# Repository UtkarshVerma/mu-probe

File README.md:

# μProbe

This probe is my personal take on the [Black Magic Debug][bmp] project's [Black Magic Probe v2.1][bmp-2.1]. I was disappointed to find out that I could not use my STLink v3 on non-ST targets[^1], even when they used the same protocol. One thing led to another and I stumbled upon the Black Magic Probe. The idea of having a configurable debugger appealed to me. This combined with an itch to work on a hardware project is what brought μProbe into existence.

> [!note]
> Please buy the official Black Magic Probe if you can! It is necessary to support the awesome work that the folks at the Black Magic project do.

## Possible future improvements

- Improve nASSERT_TVREF circuitry.
- Switch to a more powerful MCU.
- Add USB-C power negotiation.
- Add AUX connector from BMP v2.3.

## Credits

This project would not have been possible without the following resources:

- [Black Magic Debug v2.1e schematic][bmp]
- 3D models:
  - [4-pin SMT crystal osciallator by Steven Minichiello][xtal]

Lastly, I would also like to thank the warm community at 1BitSquared's Discord server for their insights and help.

[bmp]: https://black-magic.org/
[bmp-2.1]: https://black-magic.org/hardware.html#black-magic-probe-mini-v2-1-bmp21
[xtal]: https://grabcad.com/library/sitime-2016-4-pin-smt-mems-crystal-oscillator-to-20-ppm-1

[^1]: https://sourceforge.net/p/openocd/tickets/275/

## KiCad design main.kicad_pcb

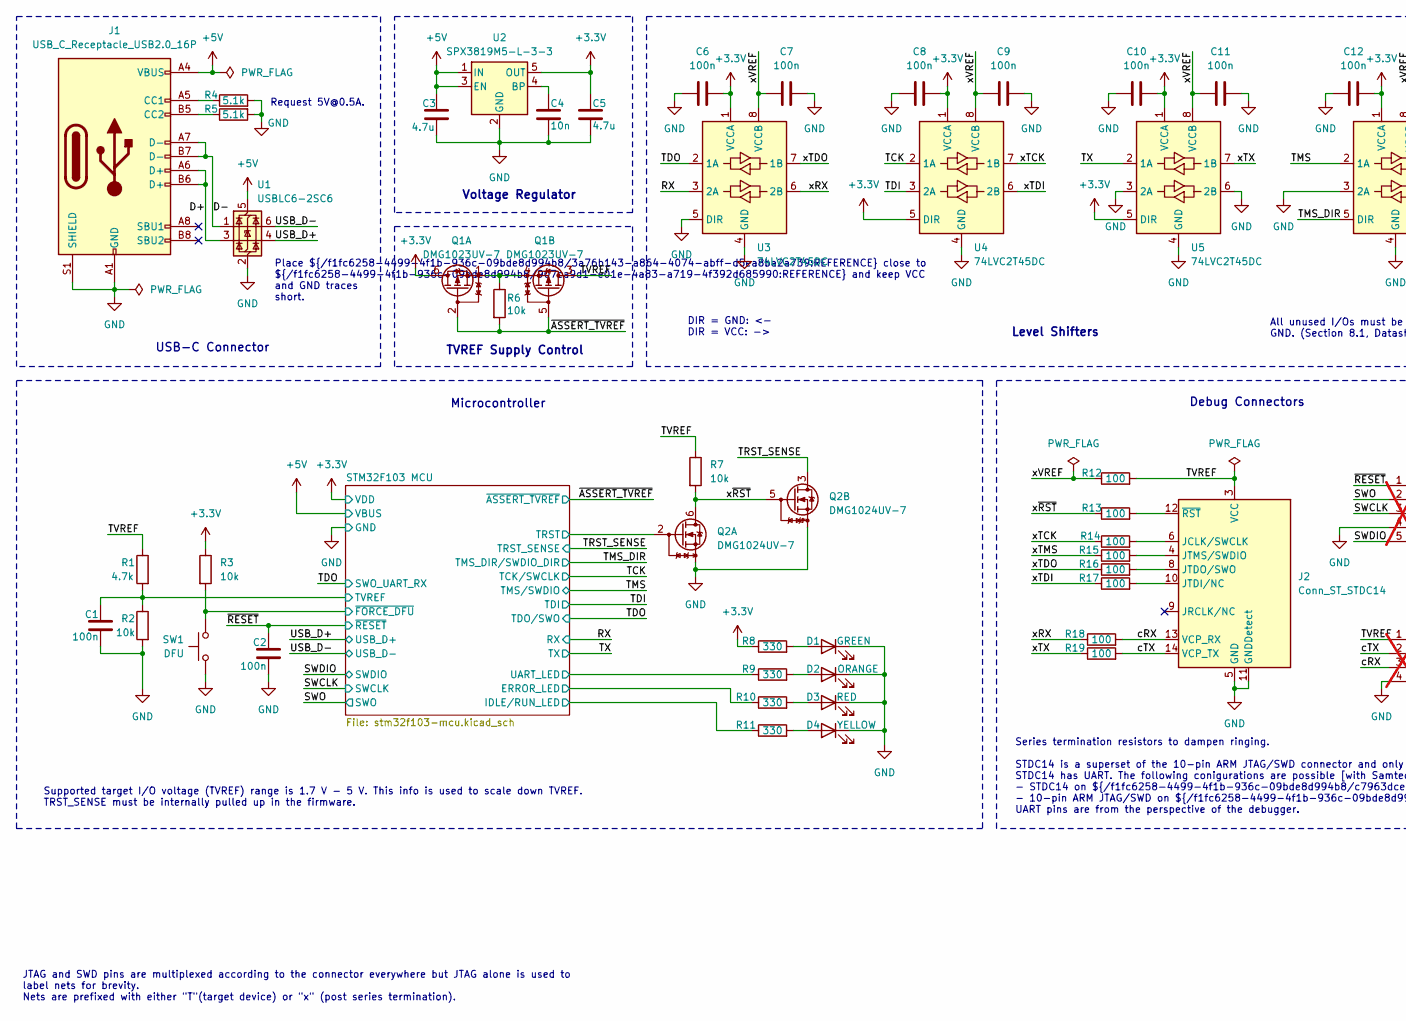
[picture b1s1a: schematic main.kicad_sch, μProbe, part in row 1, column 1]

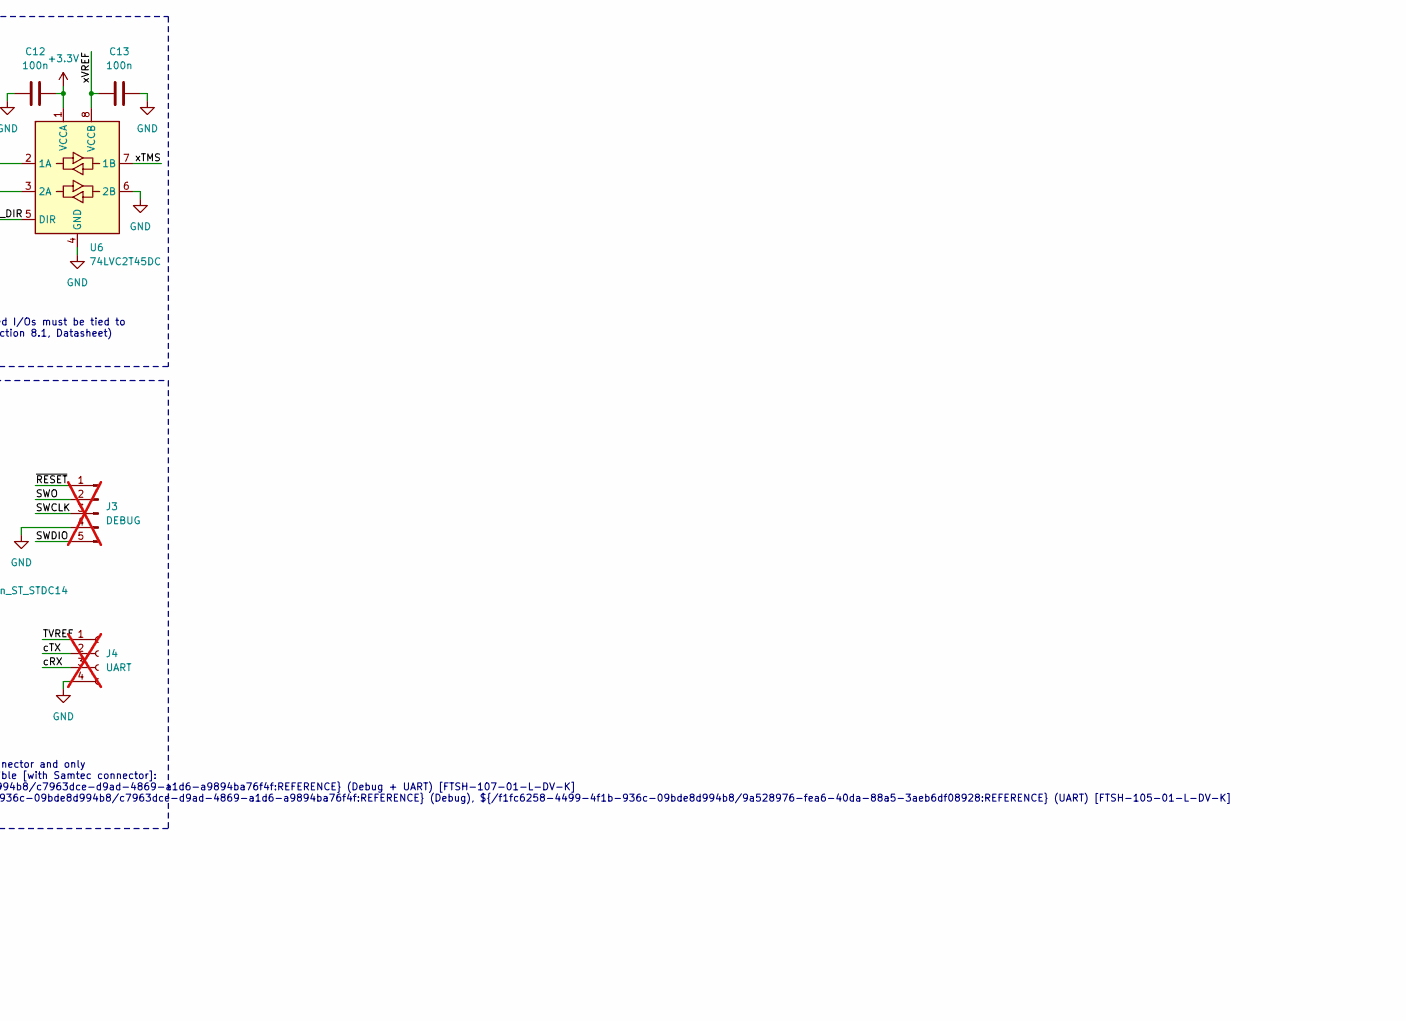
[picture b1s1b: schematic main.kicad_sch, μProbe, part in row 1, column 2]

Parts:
C1, C2, C6, C7, C8, C9, C10, C11, C12, C13: 100n; C_0402_1005Metric; LCSC Part C60474
C3, C5: 4.7u; C_0402_1005Metric; LCSC Part C23733
C4: 10n; C_0402_1005Metric; LCSC Part C15195
D1: GREEN; LED_0402_1005Metric; LCSC Part C2980183
D2: ORANGE; LED_0402_1005Metric; LCSC Part C779448
D3: RED; LED_0402_1005Metric; LCSC Part C136765
D4: YELLOW; LED_0402_1005Metric; LCSC Part C20608782
J1: USB_C_Receptacle_USB2.0_16P; USB_C_Receptacle_GCT_USB4105-xx-A_16P_TopMnt_Horizontal; LCSC Part C2988369
J2: Conn_ST_STDC14; SAMTEC_FTSH-107-01-L-DV-K; LCSC Part C46971079
J3: DEBUG; PinHeader_1x05_P1.27mm_Vertical; not fitted
J4: UART; PinHeader_1x04_P1.27mm_Vertical; not fitted
Q1: DMG1023UV-7; SOTFL50P162X60-6N; LCSC Part C212298
Q2: DMG1024UV-7; SOTFL50P162X60-6N; LCSC Part C2759893
R1: 4.7k; R_0402_1005Metric; LCSC Part C105871
R2, R3, R6, R7: 10k; R_0402_1005Metric; LCSC Part C60490
R4, R5: 5.1k; R_0402_1005Metric; LCSC Part C25905
R8, R9, R10, R11: 330; R_0402_1005Metric; LCSC Part C105875
R12, R13, R14, R15, R16, R17, R18, R19: 100; R_0402_1005Metric; LCSC Part C106232
SW1: DFU; SW_Push_SPST_NO_Alps_SKRK; LCSC Part C720477
U1: USBLC6-2SC6; SOT-23-6; LCSC Part C7519
U2: SPX3819M5-L-3-3; SOT-23-5; LCSC Part C9055
U3, U4, U5, U6: 74LVC2T45DC; VSSOP-8_2.3x2mm_P0.5mm; LCSC Part C15741

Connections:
+3.3V: C5.1, C6.1, C8.1, C10.1, C12.1, Q1.6 (D), R3.1, R8.1, U2.5 (OUT), U3.1 (VCCA), U4.1 (VCCA), U4.5 (DIR), U5.1 (VCCA), U5.5 (DIR), U6.1 (VCCA); also elsewhere on the board
+5V: C3.1, J1.A4 (VBUS), J1.A9 (VBUS), J1.B4 (VBUS), J1.B9 (VBUS), U1.5 (VBUS), U2.1 (IN), U2.3 (EN); also elsewhere on the board
/D+: J1.A6 (D+), J1.B6 (D+), U1.3 (I/O2)
/D-: J1.A7 (D-), J1.B7 (D-), U1.1 (I/O1)
/RX: U3.3 (2A); also elsewhere on the board
/STM32F103 MCU/ERROR_LED: R10.1; also elsewhere on the board
/STM32F103 MCU/IDLE/RUN_LED: R11.1; also elsewhere on the board
/STM32F103 MCU/TRST: Q2.2 (G); also elsewhere on the board
/STM32F103 MCU/TVREF: C1.1, R1.2, R2.1; also elsewhere on the board
/STM32F103 MCU/UART_LED: R9.1; also elsewhere on the board
/STM32F103 MCU/~FORCE_DFU: R3.2, SW1.2; also elsewhere on the board
/SWCLK: J3.3; also elsewhere on the board
/SWDIO: J3.5; also elsewhere on the board
/SWO: J3.2; also elsewhere on the board
/TCK: U4.2 (1A); also elsewhere on the board
/TDI: U4.3 (2A); also elsewhere on the board
/TDO: U3.2 (1A); also elsewhere on the board
/TMS: U6.2 (1A); also elsewhere on the board
/TMS_DIR: U6.5 (DIR); also elsewhere on the board
/TRST_SENSE: Q2.3 (D); also elsewhere on the board
/TVREF: J2.3 (VCC), J4.1, Q1.3 (D), R1.1, R7.1, R12.2
/TX: U5.2 (1A); also elsewhere on the board
/USB_D+: U1.4 (I/O2); also elsewhere on the board
/USB_D-: U1.6 (I/O1); also elsewhere on the board
/cRX: J2.13 (VCP_RX), J4.3, R18.2
/cTX: J2.14 (VCP_TX), J4.2, R19.2
/xRX: R18.1, U3.6 (2B)
/xTCK: R14.1, U4.7 (1B)
/xTDI: R17.1, U4.6 (2B)
/xTDO: R16.1, U3.7 (1B)
/xTMS: R15.1, U6.7 (1B)
/xTX: R19.1, U5.7 (1B)
/xVREF: C7.2, C9.2, C11.2, C13.2, R12.1, U3.8 (VCCB), U4.8 (VCCB), U5.8 (VCCB), U6.8 (VCCB)
/x~RST: Q2.5 (G), Q2.6 (D), R7.2, R13.1
/~ASSERT_TVREF: Q1.2 (G), Q1.5 (G), R6.2; also elsewhere on the board
/~RESET: C2.2, J3.1; also elsewhere on the board
GND: C1.2, C2.1, C3.2, C4.2, C5.2, C6.2, C7.1, C8.2, C9.1, C10.2, C11.1, C12.2, C13.1, D1.1 (K), D2.1 (K), D3.1 (K), D4.1 (K), J1.A1 (GND), J1.A12 (GND), J1.B1 (GND), J1.B12 (GND), J1.S1 (SHIELD), J2.5 (GND), J2.7 (GND), J2.11 (GNDDetect), J3.4, J4.4, Q2.1 (S), Q2.4 (S), R2.2, R4.2, R5.2, SW1.1, U1.2 (GND), U2.2 (GND), U3.4 (GND), U3.5 (DIR), U4.4 (GND), U5.3 (2A), U5.4 (GND), U5.6 (2B), U6.3 (2A), U6.4 (GND), U6.6 (2B); also elsewhere on the board
unnamed: D1.2 (A), R8.2
unnamed: D2.2 (A), R9.2
unnamed: D3.2 (A), R10.2
unnamed: D4.2 (A), R11.2
unnamed: J1.A5 (CC1), R4.1
unnamed: J1.B5 (CC2), R5.1
unnamed: J2.6 (JCLK/SWCLK), R14.2
unnamed: J2.10 (JTDI/NC), R17.2
unnamed: J2.8 (JTDO/SWO), R16.2
unnamed: J2.4 (JTMS/SWDIO), R15.2
unnamed: J2.12 (~RST), R13.2
unnamed: Q1.1 (S), Q1.4 (S), R6.1
unnamed: C4.1, U2.4 (BP)

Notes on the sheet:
Debug Connectors
TVREF Supply Control
Request 5V@0.5A.
Series termination resistors to dampen ringing. STDC14 is a superset of the 10-pin ARM JTAG/SWD connector and only STDC14 has UART. The following conigurations are possible [with Samtec connector]: - STDC14 on ${/f1fc6258-4499-4f1b-936c-09bde8d994b8/c7963dce-d9ad-4869-a1d6-a9894ba76f4f:REFERENCE} (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
Level Shifters
All unused I/Os must be tied to GND. (Section 8.1, Datasheet)
JTAG and SWD pins are multiplexed according to the connector everywhere but JTAG alone is used to label nets for brevity. Nets are prefixed with either "T"(target device) or "x" (post series termination).
USB-C Connector
Supported target I/O voltage (TVREF) range is 1.7 V - 5 V. This info is used to scale down TVREF. TRST_SENSE must be internally pulled up in the firmware.
Place ${/f1fc6258-4499-4f1b-936c-09bde8d994b8/3a76b143-a864-4074-abff-d5ea8ba2a739:REFERENCE} close to ${/f1fc6258-4499-4f1b-936c-09bde8d994b8/907ca9d1-e01e-4a83-a719-4f392d685990:REFERENCE} and keep VCC and GND traces short.
Voltage Regulator
DIR = GND: <- DIR = VCC: ->
Microcontroller

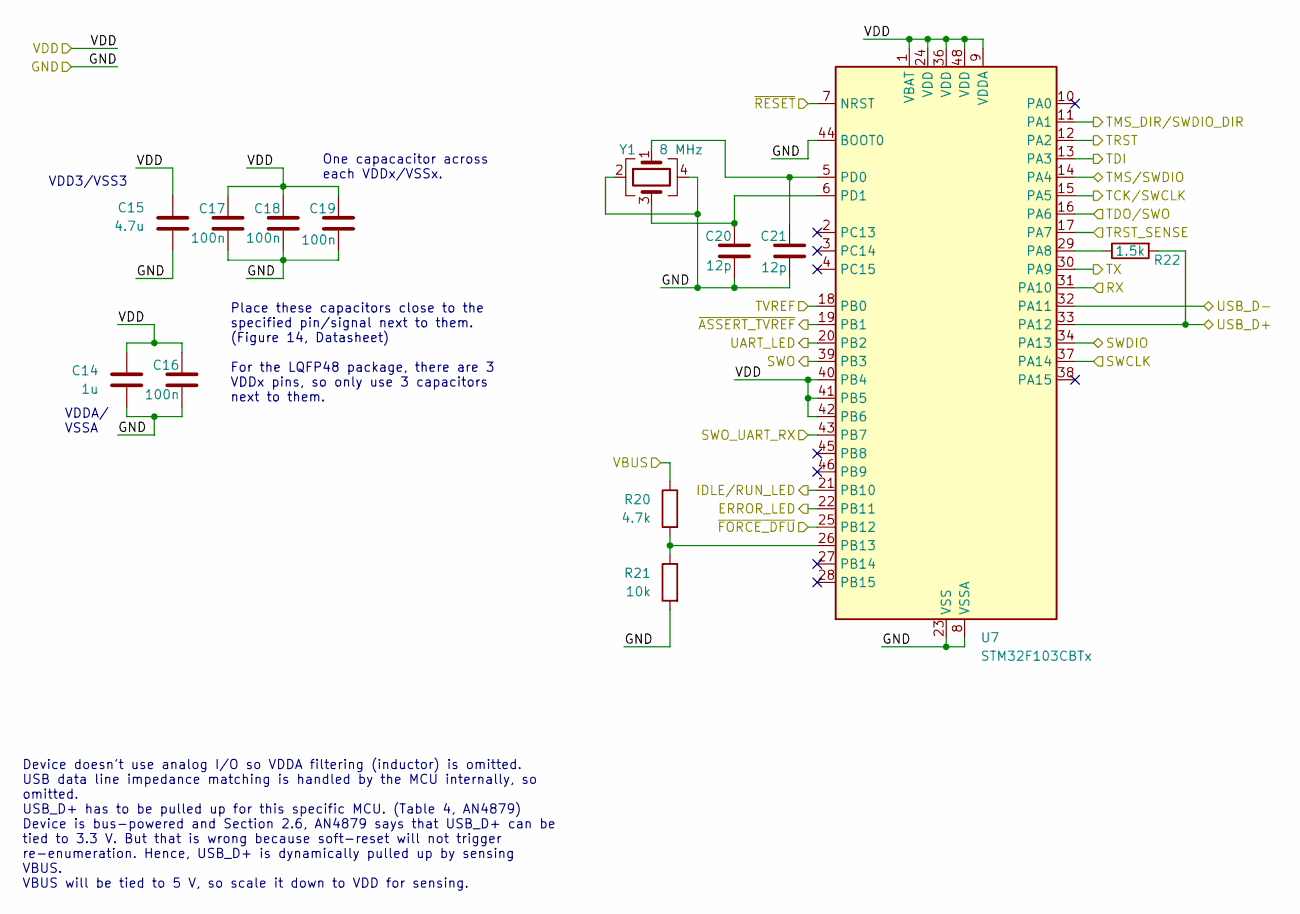
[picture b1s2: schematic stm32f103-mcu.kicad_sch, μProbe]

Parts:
C14: 1u; C_0402_1005Metric; LCSC Part C14445
C15: 4.7u; C_0402_1005Metric; LCSC Part C23733
C16, C17, C18, C19: 100n; C_0402_1005Metric; LCSC Part C60474
C20, C21: 12p; C_0402_1005Metric; LCSC Part C106201
R20: 4.7k; R_0402_1005Metric; LCSC Part C105871
R21: 10k; R_0402_1005Metric; LCSC Part C60490
R22: 1.5k; R_0402_1005Metric; LCSC Part C114759
U7: STM32F103CBTx; LQFP-48_7x7mm_P0.5mm; LCSC Part C8304
Y1: 8 MHz; Crystal_4P_GND24; LCSC Part C400090

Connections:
+3.3V: C14.1, C15.1, C16.1, C17.1, C18.1, C19.1, U7.1 (VBAT), U7.9 (VDDA), U7.24 (VDD), U7.36 (VDD), U7.40 (PB4), U7.41 (PB5), U7.42 (PB6), U7.48 (VDD); also elsewhere on the board
+5V: R20.1; also elsewhere on the board
/RX: U7.31 (PA10); also elsewhere on the board
/STM32F103 MCU/ERROR_LED: U7.22 (PB11); also elsewhere on the board
/STM32F103 MCU/IDLE/RUN_LED: U7.21 (PB10); also elsewhere on the board
/STM32F103 MCU/TRST: U7.12 (PA2); also elsewhere on the board
/STM32F103 MCU/TVREF: U7.18 (PB0); also elsewhere on the board
/STM32F103 MCU/UART_LED: U7.20 (PB2); also elsewhere on the board
/STM32F103 MCU/~FORCE_DFU: U7.25 (PB12); also elsewhere on the board
/SWCLK: U7.37 (PA14); also elsewhere on the board
/SWDIO: U7.34 (PA13); also elsewhere on the board
/SWO: U7.39 (PB3); also elsewhere on the board
/TCK: U7.15 (PA5); also elsewhere on the board
/TDI: U7.13 (PA3); also elsewhere on the board
/TDO: U7.16 (PA6), U7.43 (PB7); also elsewhere on the board
/TMS: U7.14 (PA4); also elsewhere on the board
/TMS_DIR: U7.11 (PA1); also elsewhere on the board
/TRST_SENSE: U7.17 (PA7); also elsewhere on the board
/TX: U7.30 (PA9); also elsewhere on the board
/USB_D+: R22.2, U7.33 (PA12); also elsewhere on the board
/USB_D-: U7.32 (PA11); also elsewhere on the board
/~ASSERT_TVREF: U7.19 (PB1); also elsewhere on the board
/~RESET: U7.7 (NRST); also elsewhere on the board
GND: C14.2, C15.2, C16.2, C17.2, C18.2, C19.2, C20.2, C21.2, R21.2, U7.8 (VSSA), U7.23 (VSS), U7.35 (VSS), U7.44 (BOOT0), U7.47 (VSS), Y1.2, Y1.4; also elsewhere on the board
unnamed: R22.1, U7.29 (PA8)
unnamed: R20.2, R21.1, U7.26 (PB13)
unnamed: C21.1, U7.5 (PD0), Y1.1
unnamed: C20.1, U7.6 (PD1), Y1.3

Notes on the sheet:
One capacacitor across each VDDx/VSSx.
Device doesn't use analog I/O so VDDA filtering (inductor) is omitted. USB data line impedance matching is handled by the MCU internally, so omitted. USB_D+ has to be pulled up for this specific MCU. (Table 4, AN4879) Device is bus-powered and Section 2.6, AN4879 says that USB_D+ can be tied to 3.3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
VDDA/ VSSA
VDD3/VSS3
Place these capacitors close to the specified pin/signal next to them. (Figure 14, Datasheet) For the LQFP48 package, there are 3 VDDx pins, so only use 3 capacitors next to them.

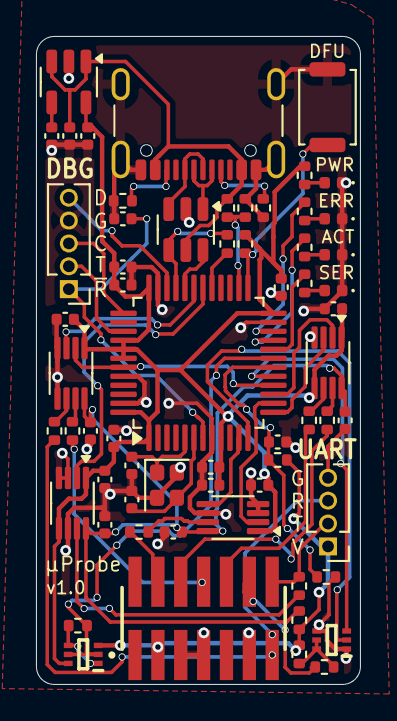
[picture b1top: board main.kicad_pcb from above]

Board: 2 copper layers, 18.0 x 36.0 mm, 62 parts (0 on the bottom side), 54 nets.

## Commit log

2025-09-07 layout: initial design with added LCSC part metadata
2025-09-07 schematic: initial design with stm32f103
2025-09-07 schematic: fix C4 LCSC part number and STM32F1 component variant
    The BMP firmware cannot be flashed onto the STM32F103C8Tx (64 KiB
    variant) due to size constraints. The STM32F103CBUx was used in the
    reference schematic but somehow got overlooked during the design.
2025-09-07 layout: update from schematic and add license
2025-09-07 layout: fix crystal footprint-model linking and update layout
2025-09-07 docs: add readme
2025-09-07 docs: add pictures to readme
2025-09-07 schematic: fix LCSC part number for STM32F1 MCU

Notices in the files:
main.kicad_pcb:
(C) 2025 Utkarsh Verma
License: CC-BY-SA 4.0
main.kicad_sch:
Licence: CC-BY-SA 4.0
